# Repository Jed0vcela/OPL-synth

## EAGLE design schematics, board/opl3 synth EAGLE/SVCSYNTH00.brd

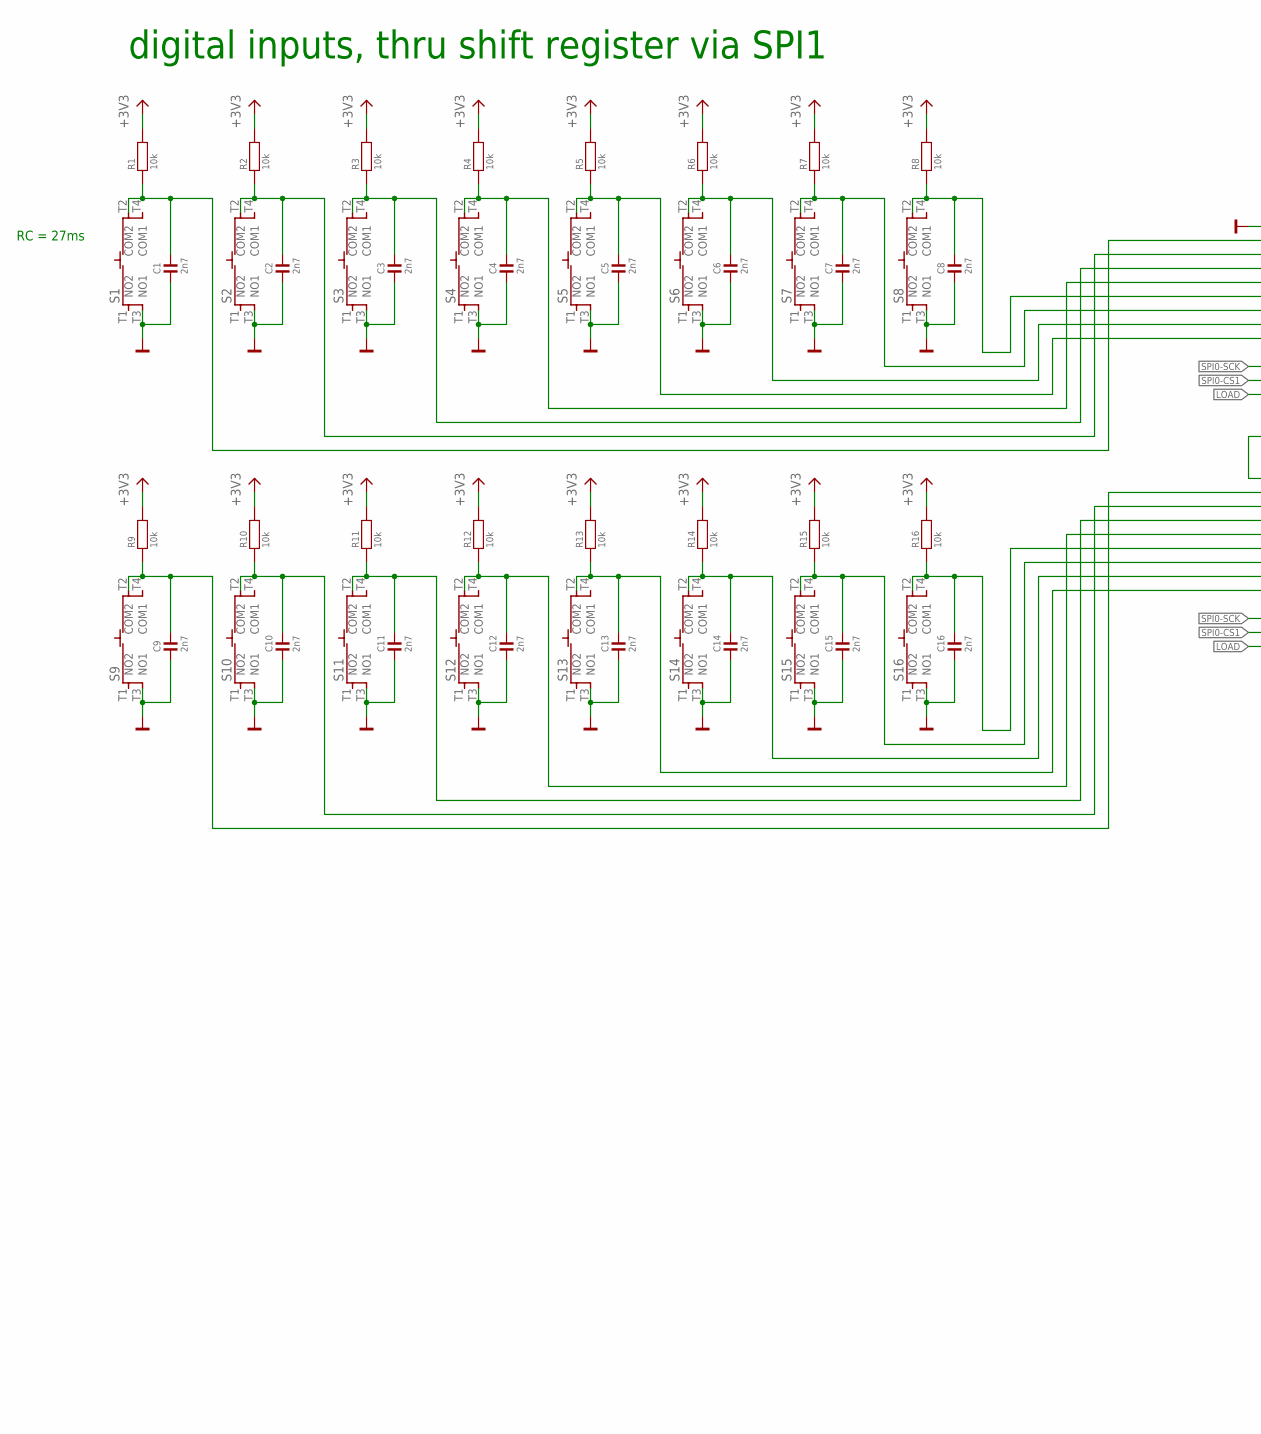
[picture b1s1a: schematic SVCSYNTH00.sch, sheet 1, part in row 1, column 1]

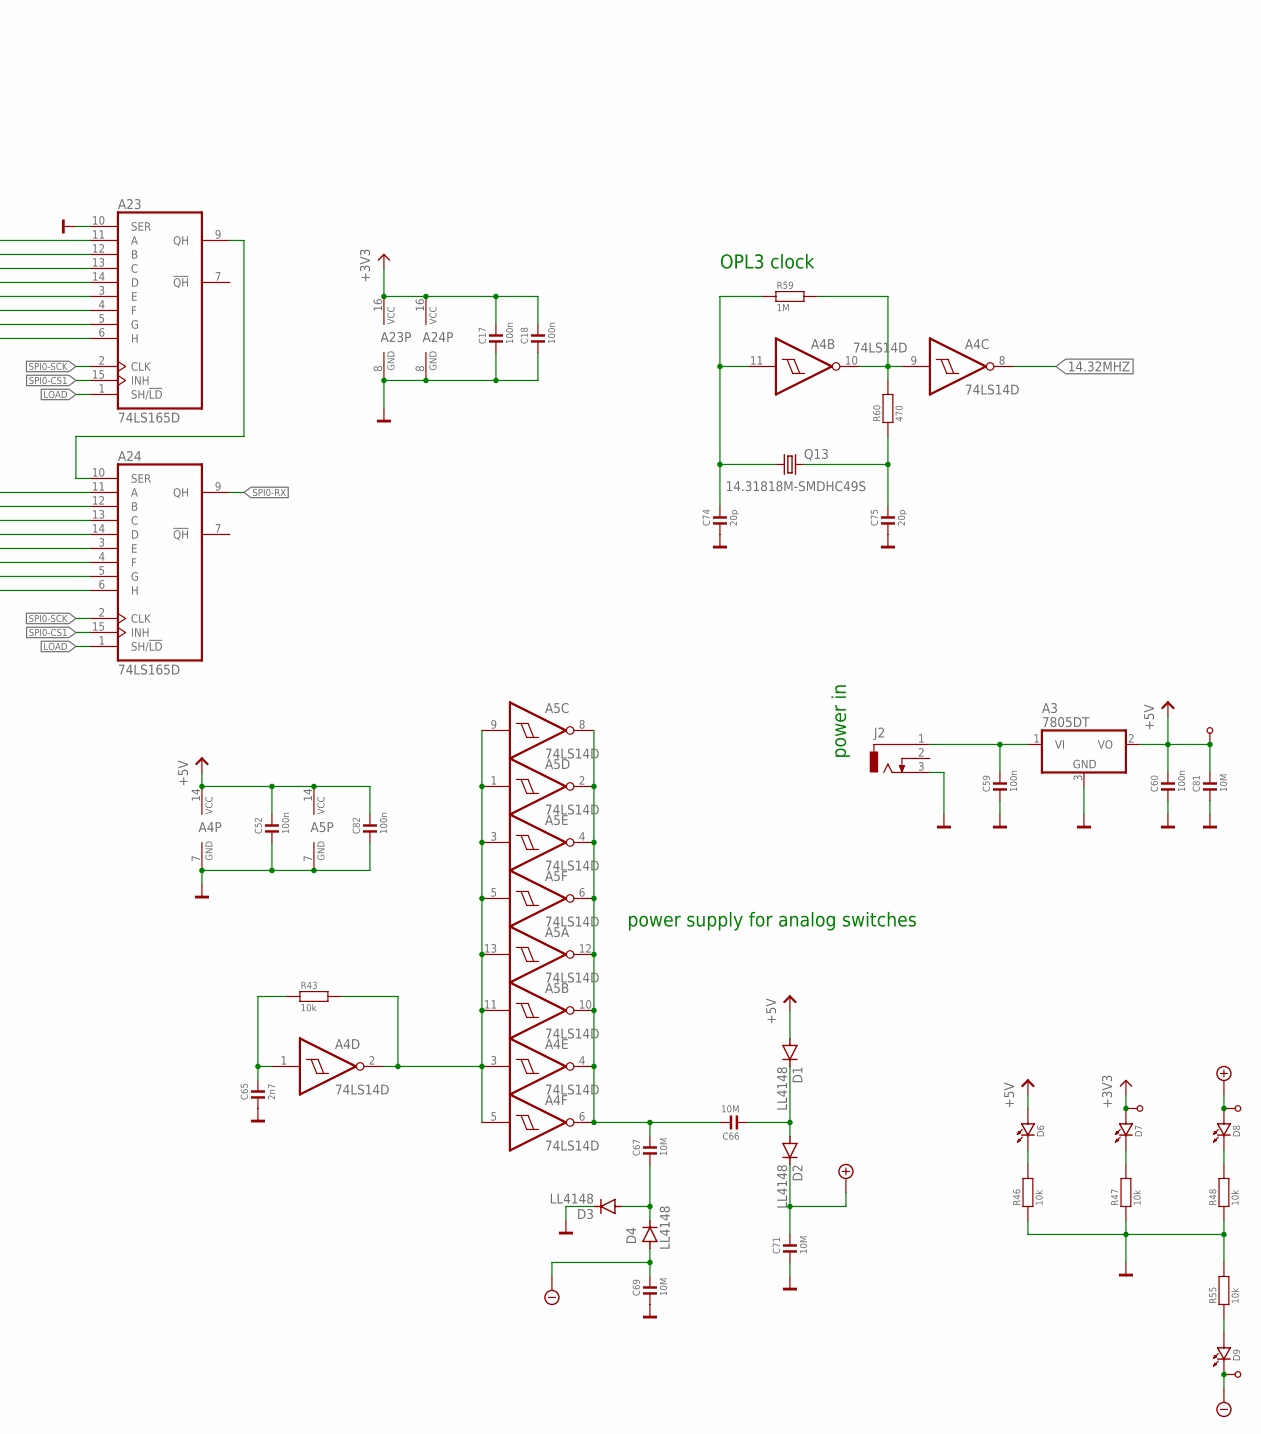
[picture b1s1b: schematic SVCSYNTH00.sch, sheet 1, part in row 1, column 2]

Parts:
A3: 7805DT; TO252
A4, A5: 74LS14D; SO14
A23, A24: 74LS165D; SO16
C1, C2, C3, C4, C5, C6, C7, C8, C9, C10, C11, C12, C13, C14, C15, C16, C65: 2n7; R0805
C17, C18, C52, C59, C60, C82: 100n; R0805
C66, C67, C69, C71, C81: 10M; R1206
C74, C75: 20p; R0805
D1, D2, D3, D4: LL4148; SOD80C
D6, D7, D8, D9: LED3MM
J2: DCJ0303
K1, K2, K3, K4: K1_0.9_1.8; K_0.9_1.8
Q13: 14.31818M-SMDHC49S; CSM-7X-DU
R1, R2, R3, R4, R5, R6, R7, R8, R9, R10, R11, R12, R13, R14, R15, R16, R43, R46, R47, R48, R55: 10k; R0805
R59: 1M; R0805
R60: 470; R0805
S1, S2, S3, S4, S5, S6, S7, S8, S9, S10, S11, S12, S13, S14, S15, S16: 101-TS6211T1603-EV; 101TS6211T1603EV

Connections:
14.32MHZ: A4.8 (O); also elsewhere on the board
+3V3: A23.16 (VCC), A24.16 (VCC), C17.2, C18.2, D7.A, K4.1, R1.1 (2), R2.1 (2), R3.1 (2), R4.1 (2), R5.1 (2), R6.1 (2), R7.1 (2), R8.1 (2), R9.1 (2), R10.1 (2), R11.1 (2), R12.1 (2), R13.1 (2), R14.1 (2), R15.1 (2), R16.1 (2); also elsewhere on the board
+5V: A3.2 (VO), A4.14 (VCC), A5.14 (VCC), C52.2, C60.2, C81.2, C82.2, D1.A, D6.A, K1.1; also elsewhere on the board
+9V: C71.2, D2.C, D8.A, K2.1; also elsewhere on the board
-5V: C69.2, D4.A, D9.K (C), K3.1; also elsewhere on the board
GND: A3.3 (GND), A4.7 (GND), A5.7 (GND), A23.8 (GND), A23.10 (SER), A24.8 (GND), C1.1, C2.1, C3.1, C4.1, C5.1, C6.1, C7.1, C8.1, C9.1, C10.1, C11.1, C12.1, C13.1, C14.1, C15.1, C16.1, C17.1, C18.1, C52.1, C59.1, C60.1, C65.1, C69.1, C71.1, C74.1, C75.1, C81.1, C82.1, D3.C, J2.3, R46.2 (1), R47.2 (1), R48.2 (1), R55.1 (2), S1.T3 (NO1), S2.T3 (NO1), S3.T3 (NO1), S4.T3 (NO1), S5.T3 (NO1), S6.T3 (NO1), S7.T3 (NO1), S8.T3 (NO1), S9.T3 (NO1), S10.T3 (NO1), S11.T3 (NO1), S12.T3 (NO1), S13.T3 (NO1), S14.T3 (NO1), S15.T3 (NO1), S16.T3 (NO1); also elsewhere on the board
LOAD: A23.1 (SH/!LD), A24.1 (SH/!LD); also elsewhere on the board
unnamed: A4.11 (I), C74.2, Q13.1, R59.2 (1)
unnamed: C75.2, Q13.2, R60.2 (1)
unnamed: A4.9 (I), A4.10 (O), R59.1 (2), R60.1 (2)
unnamed: A4.1 (I), C65.2, R43.2 (1)
unnamed: A4.2 (O), A4.3 (I), A4.5 (I), A5.1 (I), A5.3 (I), A5.5 (I), A5.9 (I), A5.11 (I), A5.13 (I), R43.1 (2)
unnamed: A4.4 (O), A4.6 (O), A5.2 (O), A5.4 (O), A5.6 (O), A5.8 (O), A5.10 (O), A5.12 (O), C66.2, C67.2
unnamed: C67.1, D3.A, D4.C
unnamed: C66.1, D1.C, D2.A
unnamed: A23.11 (A), C1.2, R1.2 (1), S1.T2 (COM2)
unnamed: A23.9 (QH), A24.10 (SER)
unnamed: A23.12 (B), C2.2, R2.2 (1), S2.T2 (COM2)
unnamed: A23.13 (C), C3.2, R3.2 (1), S3.T2 (COM2)
unnamed: A23.14 (D), C4.2, R4.2 (1), S4.T2 (COM2)
unnamed: A24.11 (A), C9.2, R9.2 (1), S9.T2 (COM2)
unnamed: A24.12 (B), C10.2, R10.2 (1), S10.T2 (COM2)
unnamed: A24.13 (C), C11.2, R11.2 (1), S11.T2 (COM2)
unnamed: A24.14 (D), C12.2, R12.2 (1), S12.T2 (COM2)
unnamed: A23.6 (H), C5.2, R5.2 (1), S5.T2 (COM2)
unnamed: A23.5 (G), C6.2, R6.2 (1), S6.T2 (COM2)
unnamed: A23.4 (F), C7.2, R7.2 (1), S7.T2 (COM2)
unnamed: A23.3 (E), C8.2, R8.2 (1), S8.T2 (COM2)
unnamed: A24.6 (H), C13.2, R13.2 (1), S13.T2 (COM2)
unnamed: A24.5 (G), C14.2, R14.2 (1), S14.T2 (COM2)
unnamed: A24.4 (F), C15.2, R15.2 (1), S15.T2 (COM2)
unnamed: A24.3 (E), C16.2, R16.2 (1), S16.T2 (COM2)
unnamed: A3.1 (VI), C59.2, J2.1
unnamed: D6.K (C), R46.1 (2)
unnamed: D7.K (C), R47.1 (2)
unnamed: D8.K (C), R48.1 (2)
unnamed: D9.A, R55.2 (1)
SPI0-CS1: A23.15 (INH), A24.15 (INH); also elsewhere on the board
SPI0-RX: A24.9 (QH); also elsewhere on the board
SPI0-SCK: A23.2 (CLK), A24.2 (CLK); also elsewhere on the board

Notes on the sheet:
RC = 27ms
digital inputs, thru shift register via SPI1
OPL3 clock
power supply for analog switches
power in

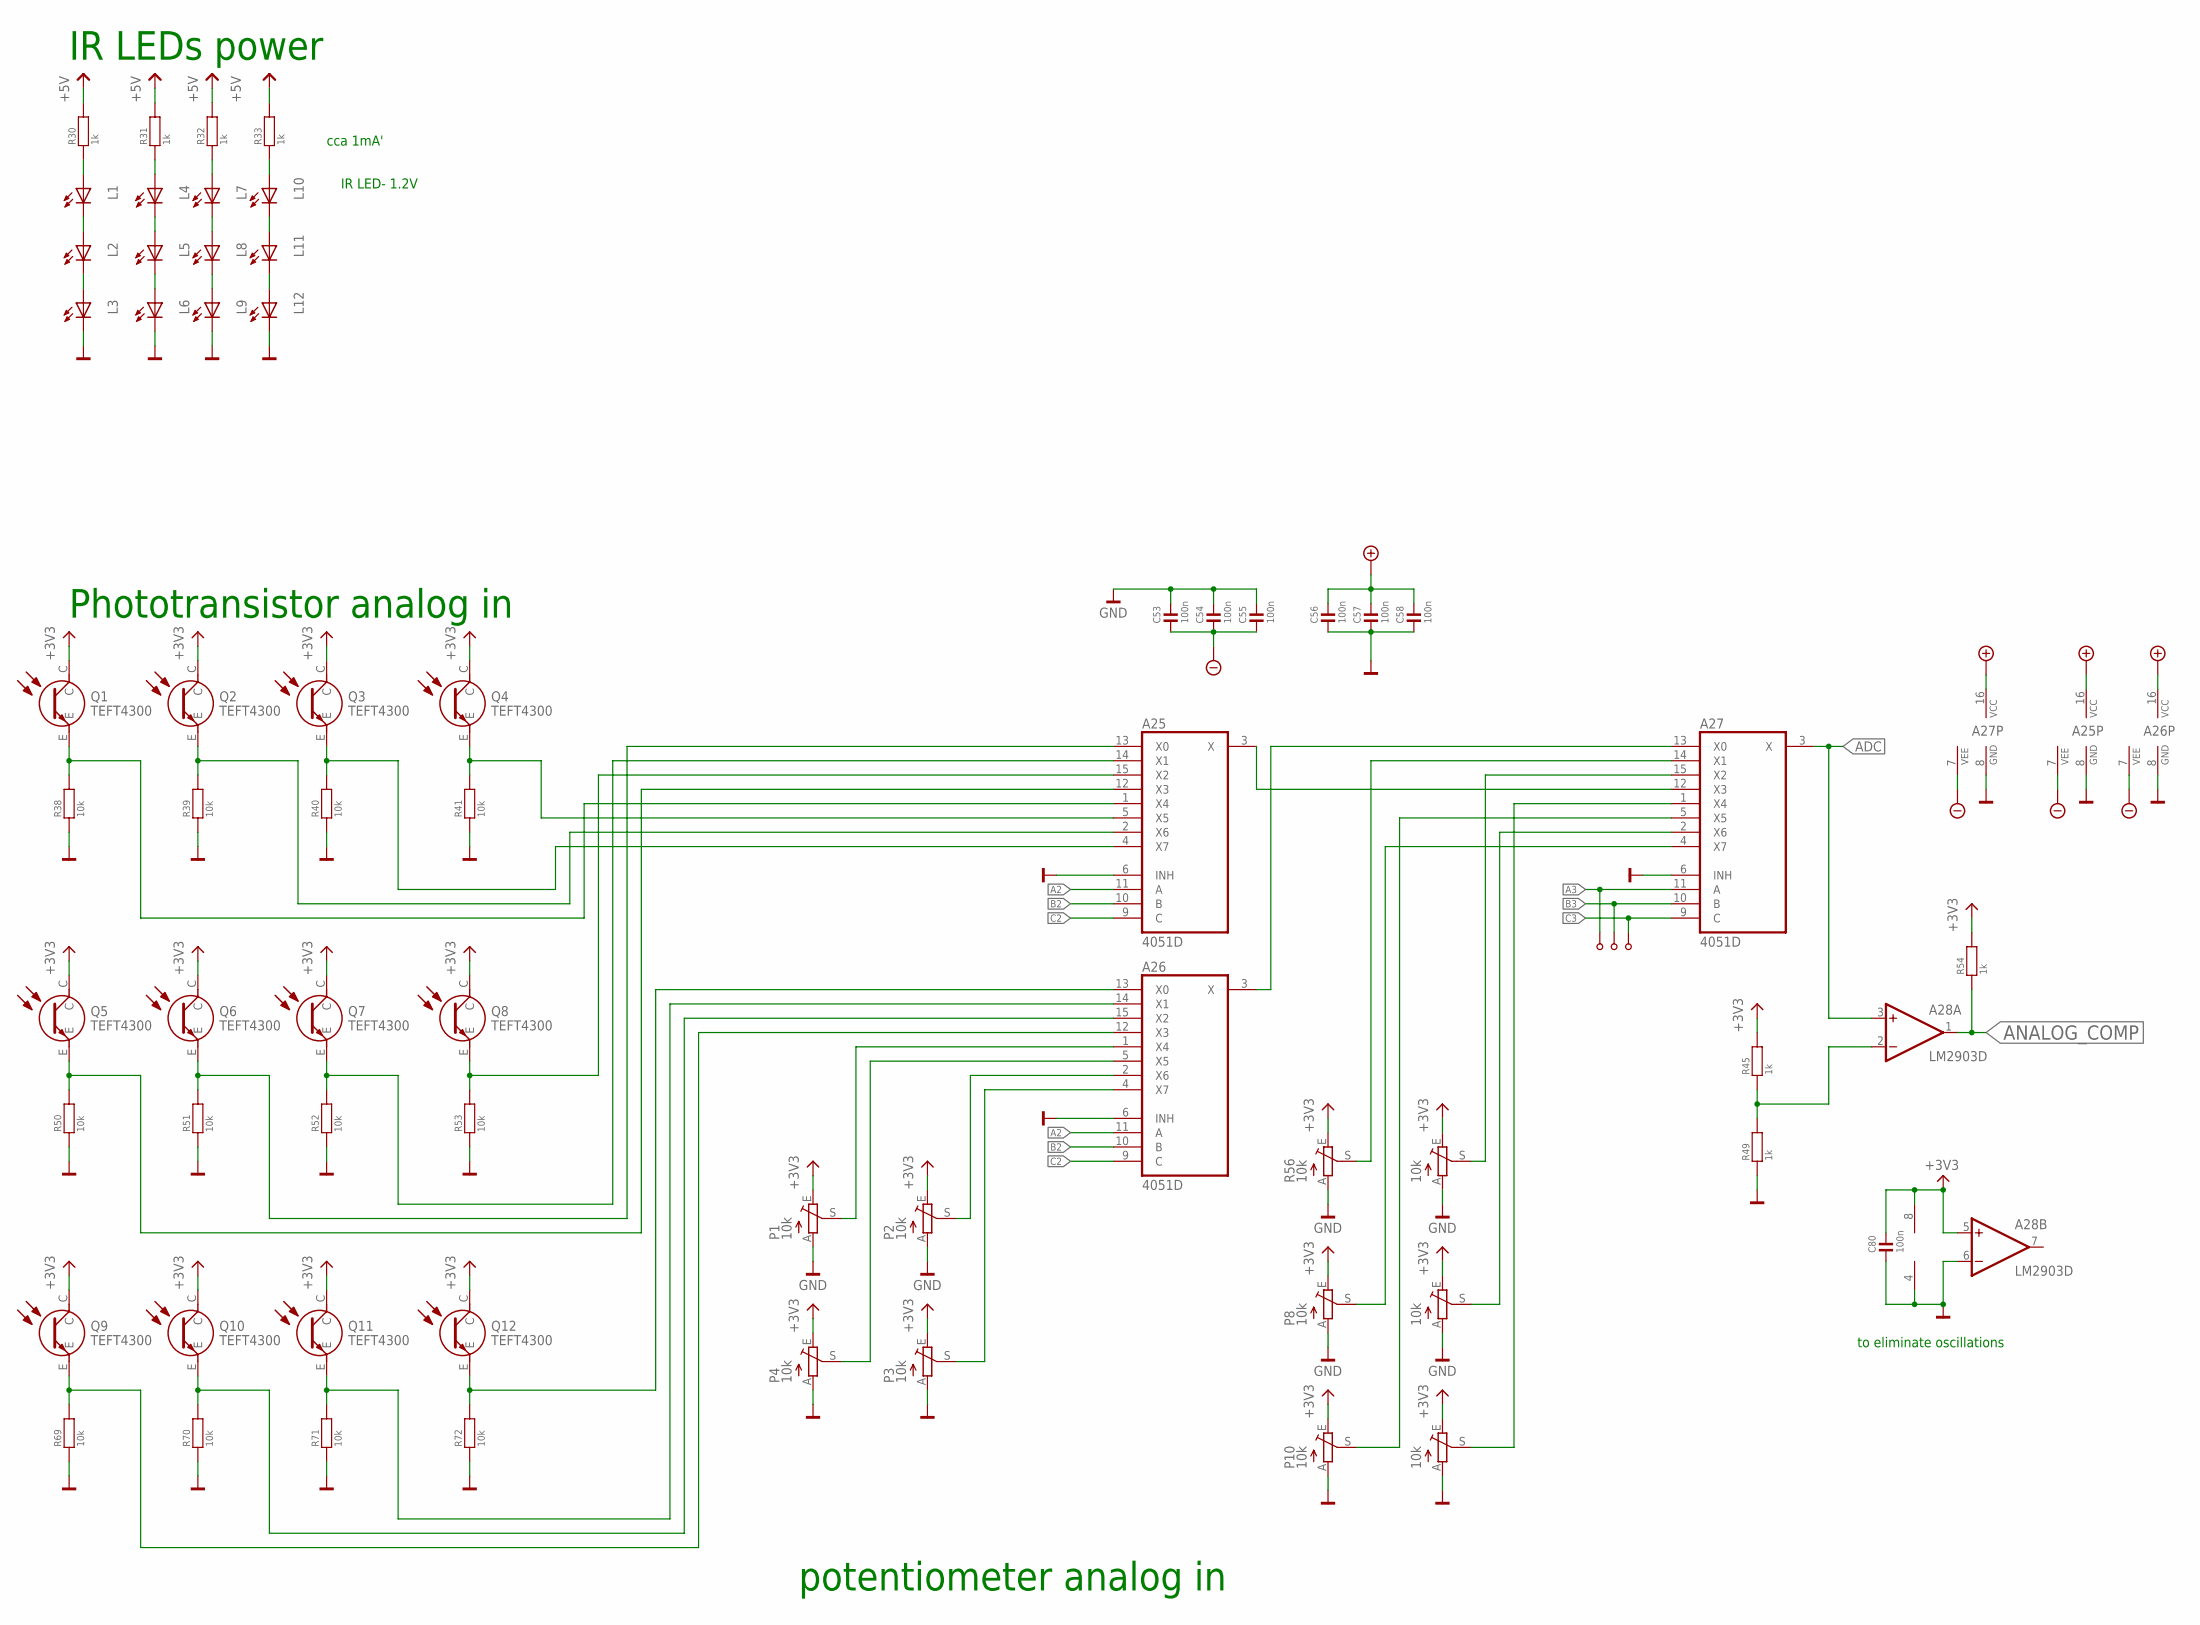
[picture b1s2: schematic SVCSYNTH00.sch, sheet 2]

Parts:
A25, A26, A27: 4051D; SO16
A28: LM2903D; SO08
C53, C54, C55, C56, C57, C58, C80: 100n; R0805
K8, K9, K10: K1_0.8_1.6; K_0.8_1.6
L1, L2, L3, L4, L5, L6, L7, L8, L9, L10, L11, L12: LED3MM
P1, P2, P3, P4, P6, P8, P10: 10k; CA6V
Q1, Q2, Q3, Q4, Q5, Q6, Q7, Q8, Q9, Q10, Q11, Q12: TEFT4300
R30, R31, R32, R33, R45, R49, R54: 1k; R0805
R38, R39, R40, R41, R50, R51, R52, R53, R69, R70, R71, R72: 10k; R0805
R56, R57, R74: 10k; CA6V

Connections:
+3V3: A28.5 (+IN), A28.8 (V+), C80.2, P1.E, P2.E, P3.E, P4.E, P6.E, P8.E, P10.E, Q1.C, Q2.C, Q3.C, Q4.C, Q5.C, Q6.C, Q7.C, Q8.C, Q9.C, Q10.C, Q11.C, Q12.C, R45.1 (2), R54.1 (2), R56.E, R57.E, R74.E; also elsewhere on the board
+5V: R30.1 (2), R31.1 (2), R32.1 (2), R33.1 (2); also elsewhere on the board
+9V: A25.16 (VCC), A26.16 (VCC), A27.16 (VCC), C56.2, C57.2, C58.2; also elsewhere on the board
-5V: A25.7 (VEE), A26.7 (VEE), A27.7 (VEE), C53.1, C54.1, C55.1; also elsewhere on the board
A2: A25.11 (A), A26.11 (A); also elsewhere on the board
A3: A27.11 (A), K8.1; also elsewhere on the board
ADC: A27.3 (X), A28.3 (+IN); also elsewhere on the board
ANALOG_COMP: A28.1 (OUT), R54.2 (1); also elsewhere on the board
B2: A25.10 (B), A26.10 (B); also elsewhere on the board
B3: A27.10 (B), K9.1; also elsewhere on the board
C2: A25.9 (C), A26.9 (C); also elsewhere on the board
C3: A27.9 (C), K10.1; also elsewhere on the board
GND: A25.6 (INH), A25.8 (GND), A26.6 (INH), A26.8 (GND), A27.6 (INH), A27.8 (GND), A28.4 (V-), A28.6 (-IN), C53.2, C54.2, C55.2, C56.1, C57.1, C58.1, C80.1, L3.K (C), L6.K (C), L9.K (C), L12.K (C), P1.A, P2.A, P3.A, P4.A, P6.A, P8.A, P10.A, R38.2 (1), R39.2 (1), R40.2 (1), R41.2 (1), R49.2 (1), R50.2 (1), R51.2 (1), R52.2 (1), R53.2 (1), R56.A, R57.A, R69.2 (1), R70.2 (1), R71.2 (1), R72.2 (1), R74.A; also elsewhere on the board
unnamed: A25.3 (X), A27.12 (X3)
unnamed: A26.3 (X), A27.13 (X0)
unnamed: A27.14 (X1), R56.S
unnamed: A27.4 (X7), P8.S
unnamed: A27.5 (X5), P10.S
unnamed: A27.15 (X2), R57.S
unnamed: L1.A, R30.2 (1)
unnamed: L1.K (C), L2.A
unnamed: L2.K (C), L3.A
unnamed: A25.5 (X5), Q4.E, R41.1 (2)
unnamed: L5.K (C), L6.A
unnamed: L4.K (C), L5.A
unnamed: L4.A, R31.2 (1)
unnamed: L7.A, R32.2 (1)
unnamed: L7.K (C), L8.A
unnamed: L8.K (C), L9.A
unnamed: L11.K (C), L12.A
unnamed: L10.K (C), L11.A
unnamed: A25.4 (X7), Q3.E, R40.1 (2)
unnamed: A25.2 (X6), Q2.E, R39.1 (2)
unnamed: A25.1 (X4), Q1.E, R38.1 (2)
unnamed: A25.15 (X2), Q8.E, R53.1 (2)
unnamed: A25.14 (X1), Q7.E, R52.1 (2)
unnamed: A25.13 (X0), Q6.E, R51.1 (2)
unnamed: A25.12 (X3), Q5.E, R50.1 (2)
unnamed: A26.13 (X0), Q12.E, R72.1 (2)
unnamed: A26.14 (X1), Q11.E, R71.1 (2)
unnamed: A26.15 (X2), Q10.E, R70.1 (2)
unnamed: A26.12 (X3), Q9.E, R69.1 (2)
unnamed: A26.1 (X4), P1.S
unnamed: A26.5 (X5), P4.S
unnamed: A26.2 (X6), P2.S
unnamed: A26.4 (X7), P3.S
unnamed: A27.2 (X6), P6.S
unnamed: A27.1 (X4), R74.S
unnamed: A28.2 (-IN), R45.2 (1), R49.1 (2)
unnamed: L10.A, R33.2 (1)

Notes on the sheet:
Phototransistor analog in
potentiometer analog in
to eliminate oscillations
IR LED- 1.2V
cca 1mA'
IR LEDs power

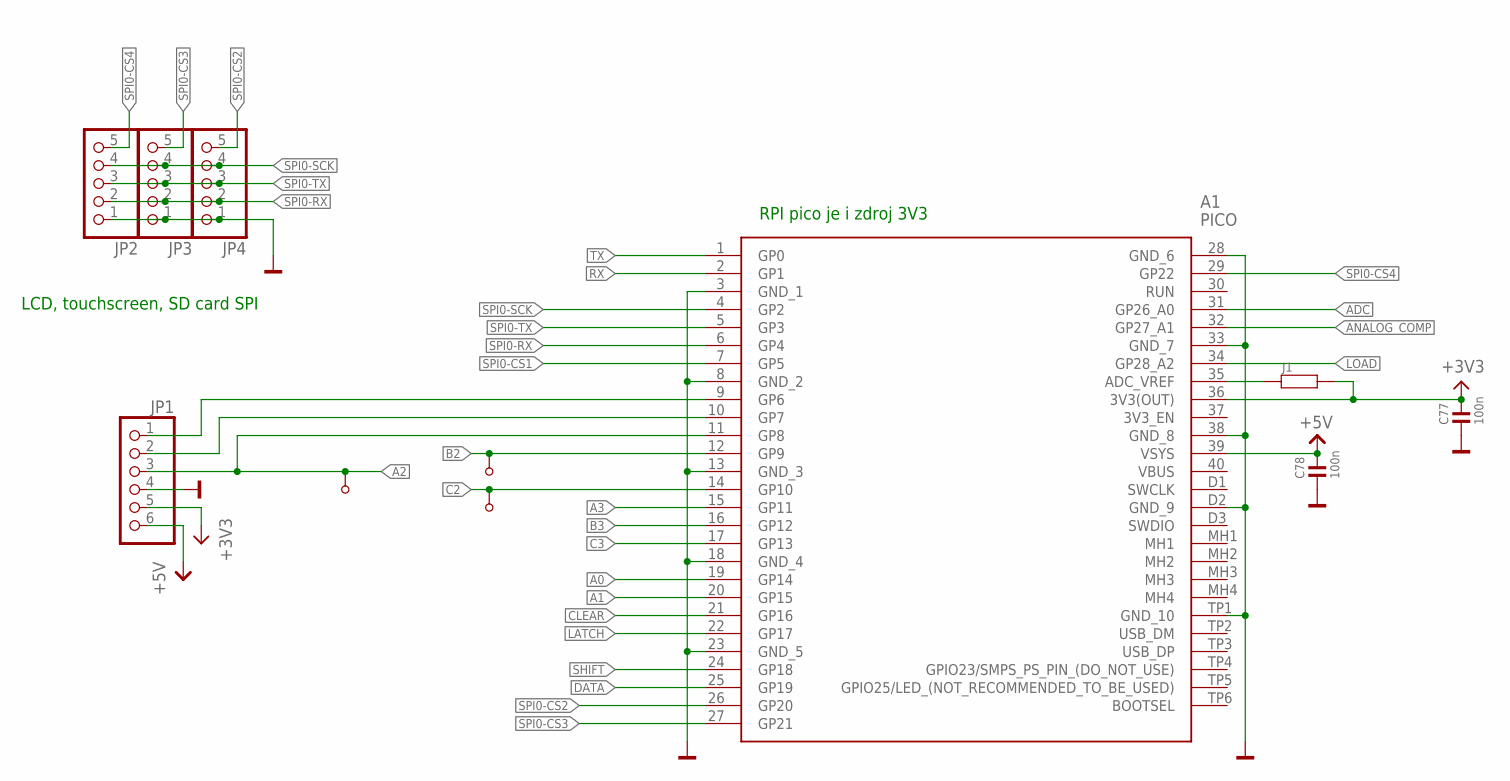
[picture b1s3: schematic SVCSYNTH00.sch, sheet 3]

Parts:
A1: PICO
C77, C78: 100n; R0805
J1: R0402
JP1: PINHD-1X6; 1X06
JP2, JP3, JP4: PINHD-1X5; 1X05
K5, K6, K7: K1_1.0_2.2; K_1.0_2.2

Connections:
+3V3: A1.36 (3V3(OUT)), C77.2, J1.2, JP1.5; also elsewhere on the board
+5V: A1.39 (VSYS), C78.2, JP1.6; also elsewhere on the board
A0: A1.19 (GP14); also elsewhere on the board
A1: A1.20 (GP15); also elsewhere on the board
A2: A1.11 (GP8), JP1.3, K5.1; also elsewhere on the board
A3: A1.15 (GP11); also elsewhere on the board
ADC: A1.31 (GP26_A0); also elsewhere on the board
ANALOG_COMP: A1.32 (GP27_A1); also elsewhere on the board
B2: A1.12 (GP9), K7.1; also elsewhere on the board
B3: A1.16 (GP12); also elsewhere on the board
C2: A1.14 (GP10), K6.1; also elsewhere on the board
C3: A1.17 (GP13); also elsewhere on the board
CLEAR: A1.21 (GP16); also elsewhere on the board
DATA: A1.25 (GP19); also elsewhere on the board
GND: A1.3 (GND_1), A1.8 (GND_2), A1.13 (GND_3), A1.18 (GND_4), A1.23 (GND_5), A1.28 (GND_6), A1.33 (GND_7), A1.38 (GND_8), A1.D2 (GND_9), A1.TP1 (GND_10), C77.1, C78.1, JP1.4, JP2.1, JP3.1, JP4.1; also elsewhere on the board
LATCH: A1.22 (GP17); also elsewhere on the board
LOAD: A1.34 (GP28_A2); also elsewhere on the board
unnamed: A1.35 (ADC_VREF), J1.1
unnamed: A1.9 (GP6), JP1.1
unnamed: A1.10 (GP7), JP1.2
RX: A1.2 (GP1); also elsewhere on the board
SHIFT: A1.24 (GP18); also elsewhere on the board
SPI0-CS1: A1.7 (GP5); also elsewhere on the board
SPI0-CS2: A1.26 (GP20), JP4.5
SPI0-CS3: A1.27 (GP21), JP3.5
SPI0-CS4: A1.29 (GP22), JP2.5
SPI0-RX: A1.6 (GP4), JP2.2, JP3.2, JP4.2; also elsewhere on the board
SPI0-SCK: A1.4 (GP2), JP2.4, JP3.4, JP4.4; also elsewhere on the board
SPI0-TX: A1.5 (GP3), JP2.3, JP3.3, JP4.3
TX: A1.1 (GP0); also elsewhere on the board

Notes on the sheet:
LCD, touchscreen, SD card SPI
RPI pico je i zdroj 3V3

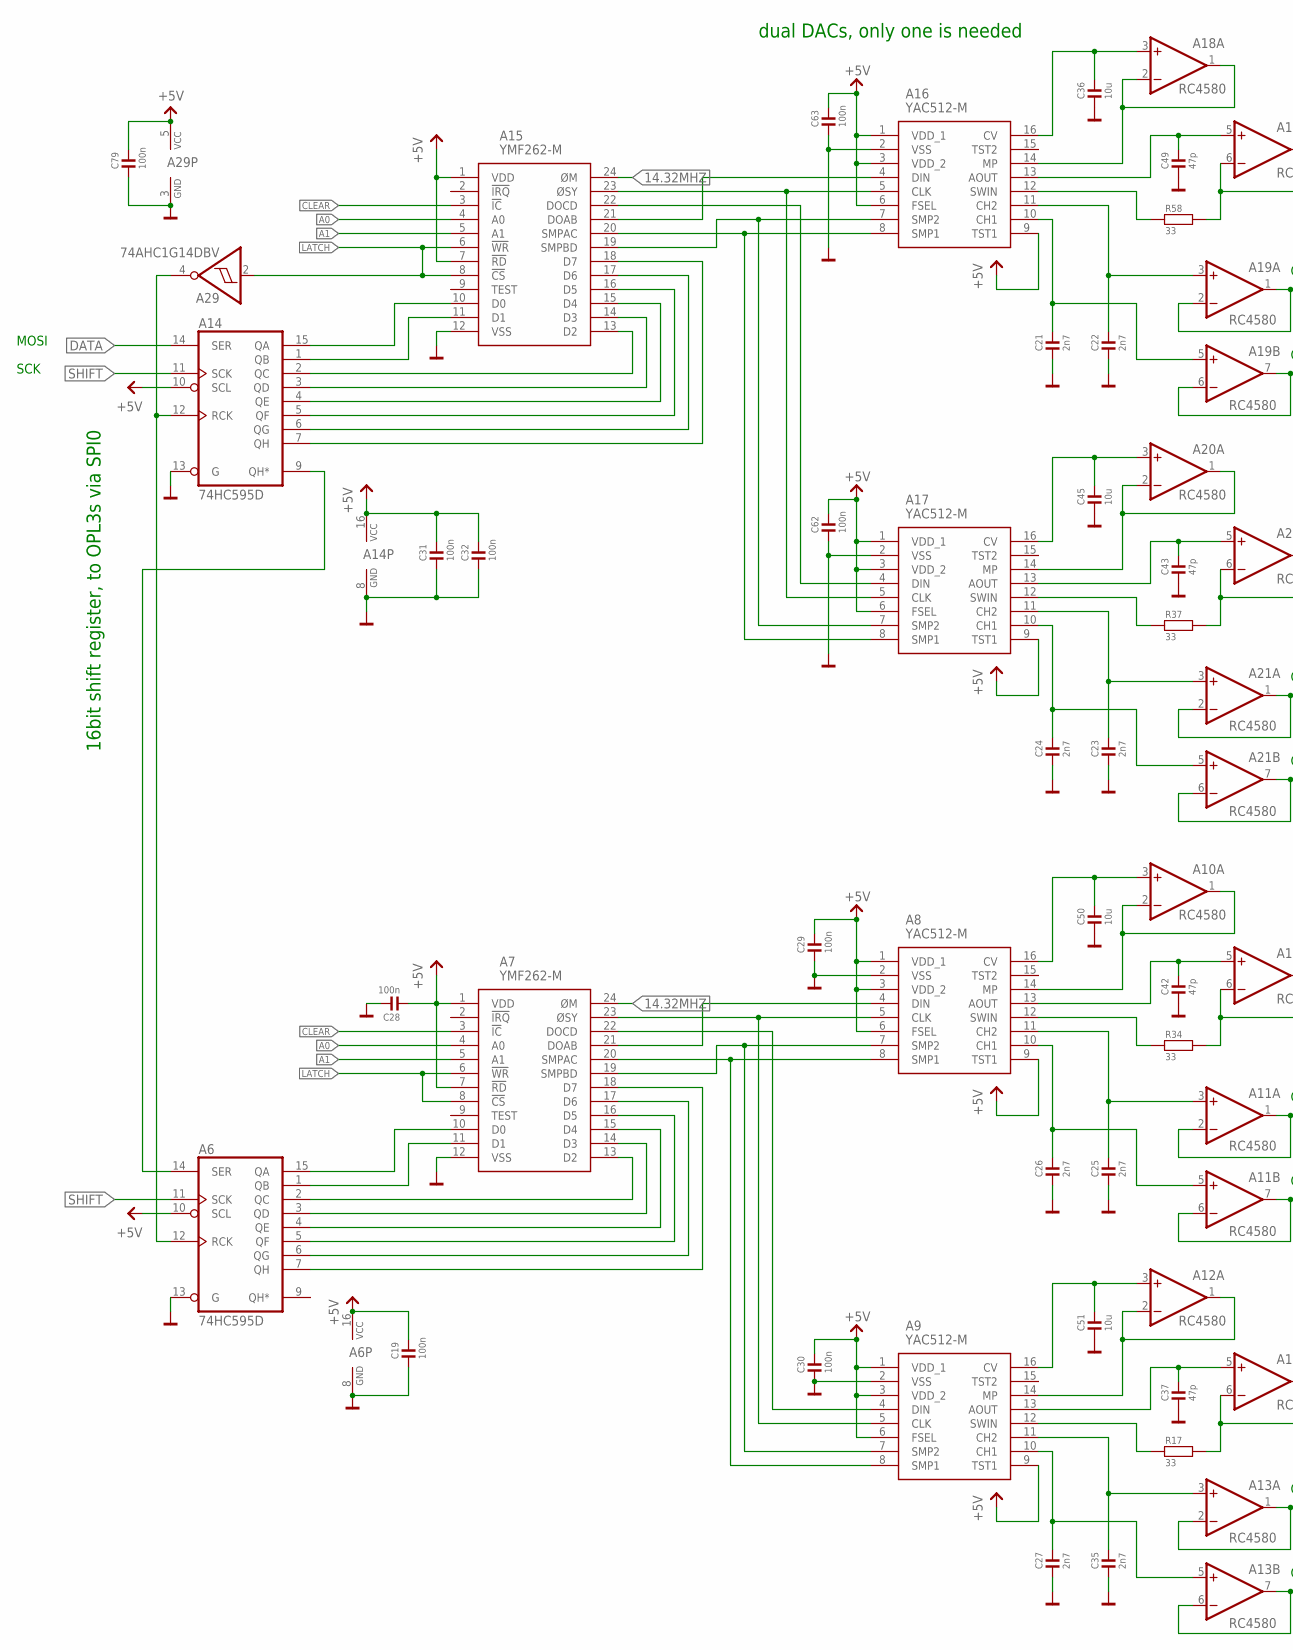
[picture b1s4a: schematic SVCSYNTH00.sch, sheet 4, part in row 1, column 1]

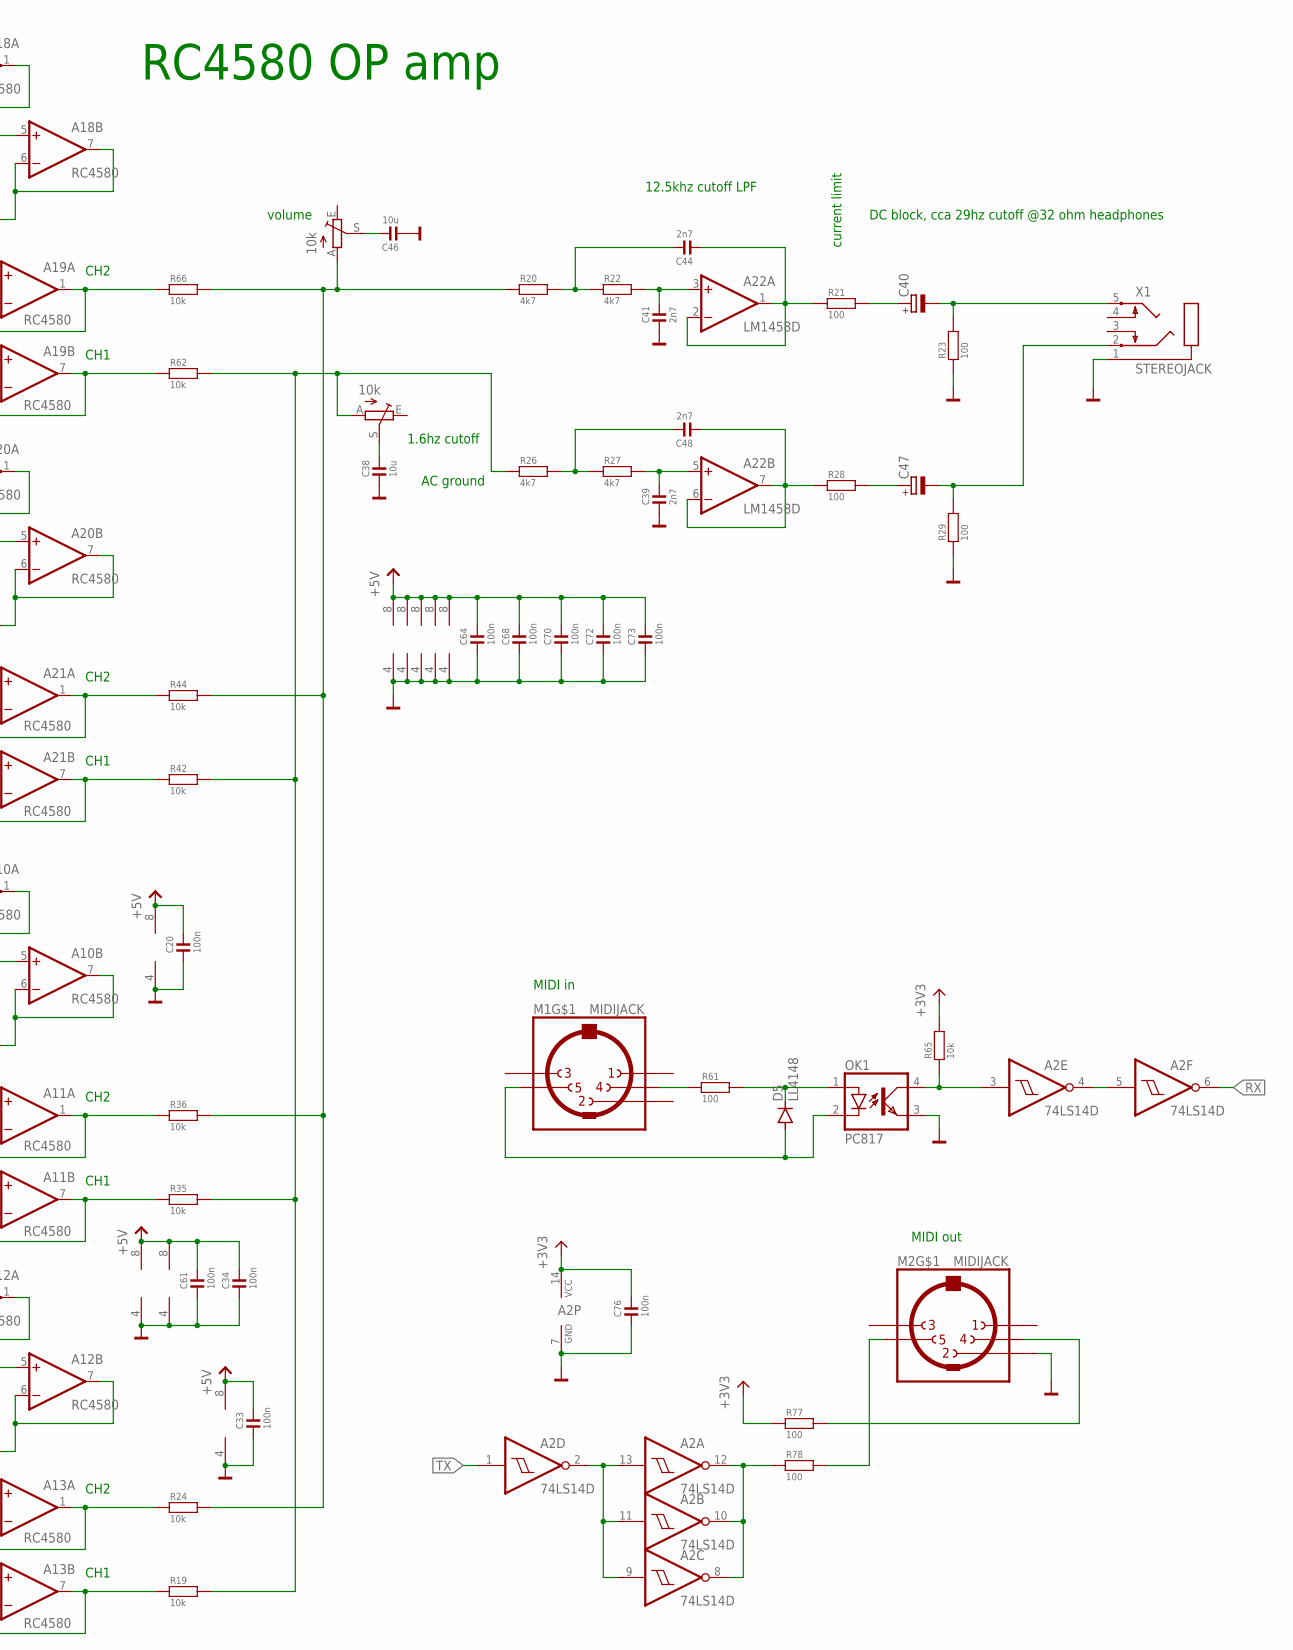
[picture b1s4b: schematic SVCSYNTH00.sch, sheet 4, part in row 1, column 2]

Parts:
A2: 74LS14D; SO14
A6, A14: 74HC595D; SO16
A7, A15: YMF262-M; SOIC127P1180X250-24N
A8, A9, A16, A17: YAC512-M; SOIC127P780X230-16N
A10, A11, A12, A13, A18, A19, A20, A21: RC4580; SO08
A22: LM1458D; SO08
A29: 74AHC1G14DBV; SOT23-5
C19, C20, C28, C29, C30, C31, C32, C33, C34, C61, C62, C63, C64, C68, C70, C72, C73, C76, C79: 100n; R0805
C21, C22, C23, C24, C25, C26, C27, C35, C39, C41, C44, C48: 2n7; R0805
C36, C38, C45, C46, C50, C51: 10u; R0805
C37, C42, C43, C49: 47p; R0805
C40, C47: CPOL-EUE3.5-8; E3,5-8
D5: LL4148; SOD80C
M1, M2: MIDIJACK; CP-2350
OK1: PC817; DIL04
R17, R34, R37, R58: 33; R0805
R18, R25: 10k; CA6V
R19, R24, R35, R36, R42, R44, R62, R65, R66: 10k; R0805
R20, R22, R26, R27: 4k7; R0805
R21, R23, R28, R29, R61, R77, R78: 100; R0805
X1: STEREOJACK; STX3100

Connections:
14.32MHZ: A7.24 (ØM), A15.24 (ØM); also elsewhere on the board
+3V3: A2.14 (VCC), C76.2, R65.1 (2), R77.2 (1); also elsewhere on the board
+5V: A6.10 (SCL), A6.16 (VCC), A7.1 (VDD), A7.7 (!RD), A8.1 (VDD_1), A8.3 (VDD_2), A8.6 (FSEL), A8.9 (TST1), A9.1 (VDD_1), A9.3 (VDD_2), A9.6 (FSEL), A9.9 (TST1), A10.8 (V+), A11.8 (V+), A12.8 (V+), A13.8 (V+), A14.10 (SCL), A14.16 (VCC), A15.1 (VDD), A15.7 (!RD), A16.1 (VDD_1), A16.3 (VDD_2), A16.6 (FSEL), A16.9 (TST1), A17.1 (VDD_1), A17.3 (VDD_2), A17.6 (FSEL), A17.9 (TST1), A18.8 (V+), A19.8 (V+), A20.8 (V+), A21.8 (V+), A22.8 (V+), A29.5 (VCC), C19.2, C20.2, C28.1, C29.2, C30.2, C31.2, C32.2, C33.2, C34.2, C61.2, C62.2, C63.2, C64.2, C68.2, C70.2, C72.2, C73.2, C79.2; also elsewhere on the board
A0: A7.4 (A0), A15.4 (A0); also elsewhere on the board
A1: A7.5 (A1), A15.5 (A1); also elsewhere on the board
CLEAR: A7.3 (!IC), A15.3 (!IC); also elsewhere on the board
DATA: A14.14 (SER); also elsewhere on the board
GND: A2.7 (GND), A6.8 (GND), A6.13 (G), A7.12 (VSS), A8.2 (VSS), A9.2 (VSS), A10.4 (V-), A11.4 (V-), A12.4 (V-), A13.4 (V-), A14.8 (GND), A14.13 (G), A15.12 (VSS), A16.2 (VSS), A17.2 (VSS), A18.4 (V-), A19.4 (V-), A20.4 (V-), A21.4 (V-), A22.4 (V-), A29.3 (GND), C19.1, C20.1, C21.1, C22.1, C23.1, C24.1, C25.1, C26.1, C27.1, C28.2, C29.1, C30.1, C31.1, C32.1, C33.1, C34.1, C35.1, C36.1, C37.1, C38.1, C39.1, C41.1, C42.1, C43.1, C45.1, C46.1, C49.1, C50.1, C51.1, C61.1, C62.1, C63.1, C64.1, C68.1, C70.1, C72.1, C73.1, C76.1, C79.1, M2.2, OK1.3 (EMIT), R23.2 (1), R29.2 (1), X1.1; also elsewhere on the board
LATCH: A7.6 (!WR), A7.8 (!CS), A15.6 (!WR), A15.8 (!CS), A29.2 (I); also elsewhere on the board
unnamed: A16.13 (AOUT), A18.5 (+IN), C49.2
unnamed: A16.14 (MP), A18.1 (OUT), A18.2 (-IN)
unnamed: A16.16 (CV), A18.3 (+IN), C36.2
unnamed: A18.6 (-IN), A18.7 (OUT), R58.1 (2)
unnamed: A16.12 (SWIN), R58.2 (1)
unnamed: A16.10 (CH1), A19.5 (+IN), C21.2
unnamed: A16.11 (CH2), A19.3 (+IN), C22.2
unnamed: A19.1 (OUT), A19.2 (-IN), R66.2 (1)
unnamed: A19.6 (-IN), A19.7 (OUT), R62.2 (1)
unnamed: A14.15 (QA), A15.10 (D0)
unnamed: A14.1 (QB), A15.11 (D1)
unnamed: A14.2 (QC), A15.13 (D2)
unnamed: A14.3 (QD), A15.14 (D3)
unnamed: A14.4 (QE), A15.15 (D4)
unnamed: A14.5 (QF), A15.16 (D5)
unnamed: A14.6 (QG), A15.17 (D6)
unnamed: A14.7 (QH), A15.18 (D7)
unnamed: A15.20 (SMPAC), A16.8 (SMP1), A17.8 (SMP1)
unnamed: A8.14 (MP), A10.1 (OUT), A10.2 (-IN)
unnamed: A15.21 (DOAB), A16.4 (DIN)
unnamed: A15.23 (ØSY), A16.5 (CLK), A17.5 (CLK)
unnamed: A17.14 (MP), A20.1 (OUT), A20.2 (-IN)
unnamed: A6.12 (RCK), A14.12 (RCK), A29.4 (O)
unnamed: A17.16 (CV), A20.3 (+IN), C45.2
unnamed: A17.13 (AOUT), A20.5 (+IN), C43.2
unnamed: A20.6 (-IN), A20.7 (OUT), R37.1 (2)
unnamed: A17.12 (SWIN), R37.2 (1)
unnamed: A17.10 (CH1), A21.5 (+IN), C24.2
unnamed: A17.11 (CH2), A21.3 (+IN), C23.2
unnamed: A21.1 (OUT), A21.2 (-IN), R44.2 (1)
unnamed: A21.6 (-IN), A21.7 (OUT), R42.2 (1)
unnamed: A15.19 (SMPBD), A16.7 (SMP2), A17.7 (SMP2)
unnamed: A15.22 (DOCD), A17.4 (DIN)
unnamed: A8.16 (CV), A10.3 (+IN), C50.2
unnamed: A8.13 (AOUT), A10.5 (+IN), C42.2
unnamed: A10.6 (-IN), A10.7 (OUT), R34.1 (2)
unnamed: A8.12 (SWIN), R34.2 (1)
unnamed: A8.10 (CH1), A11.5 (+IN), C26.2
unnamed: A8.11 (CH2), A11.3 (+IN), C25.2
unnamed: A11.1 (OUT), A11.2 (-IN), R36.2 (1)
unnamed: A11.6 (-IN), A11.7 (OUT), R35.2 (1)
unnamed: A6.15 (QA), A7.10 (D0)
unnamed: A6.1 (QB), A7.11 (D1)
unnamed: A6.2 (QC), A7.13 (D2)
unnamed: A6.3 (QD), A7.14 (D3)
unnamed: A6.4 (QE), A7.15 (D4)
unnamed: A6.5 (QF), A7.16 (D5)
unnamed: A6.6 (QG), A7.17 (D6)
unnamed: A6.7 (QH), A7.18 (D7)
unnamed: A7.20 (SMPAC), A8.8 (SMP1), A9.8 (SMP1)
unnamed: A7.21 (DOAB), A8.4 (DIN)
unnamed: A7.23 (ØSY), A8.5 (CLK), A9.5 (CLK)
unnamed: A9.14 (MP), A12.1 (OUT), A12.2 (-IN)
unnamed: A9.16 (CV), A12.3 (+IN), C51.2
unnamed: A9.13 (AOUT), A12.5 (+IN), C37.2
unnamed: A12.6 (-IN), A12.7 (OUT), R17.1 (2)
unnamed: A9.12 (SWIN), R17.2 (1)
unnamed: A9.10 (CH1), A13.5 (+IN), C27.2
unnamed: A9.11 (CH2), A13.3 (+IN), C35.2
unnamed: A13.1 (OUT), A13.2 (-IN), R24.2 (1)
unnamed: A13.6 (-IN), A13.7 (OUT), R19.2 (1)
unnamed: A7.19 (SMPBD), A8.7 (SMP2), A9.7 (SMP2)
unnamed: A7.22 (DOCD), A9.4 (DIN)
unnamed: A6.14 (SER), A14.9 (QH*)
unnamed: A22.3 (+IN), C41.2, R22.1 (2)
unnamed: R19.1 (2), R25.A, R26.2 (1), R35.1 (2), R42.1 (2), R62.1 (2)
unnamed: C38.2, R25.S
unnamed: R18.A, R20.2 (1), R24.1 (2), R36.1 (2), R44.1 (2), R66.1 (2)
unnamed: C46.2, R18.S
unnamed: C44.2, R20.1 (2), R22.2 (1)
unnamed: A22.5 (+IN), C39.2, R27.1 (2)
unnamed: A22.1 (OUT), A22.2 (-IN), C44.1, R21.2 (1)
unnamed: C48.2, R26.1 (2), R27.2 (1)
unnamed: A22.6 (-IN), A22.7 (OUT), C48.1, R28.2 (1)
unnamed: C40.+, R21.1 (2)
unnamed: C40.-, R23.1 (2), X1.5
unnamed: C47.+, R28.1 (2)
unnamed: C47.-, R29.1 (2), X1.2
unnamed: A2.2 (O), A2.9 (I), A2.11 (I), A2.13 (I)
unnamed: A2.4 (O), A2.5 (I)
unnamed: M2.5, R78.1 (2)
unnamed: A2.8 (O), A2.10 (O), A2.12 (O), R78.2 (1)
unnamed: M1.4, R61.2 (1)
unnamed: M2.4, R77.1 (2)
unnamed: D5.A, M1.5, OK1.2 (C)
unnamed: D5.C, OK1.1 (A), R61.1 (2)
unnamed: A2.3 (I), OK1.4 (COL), R65.2 (1)
RX: A2.6 (O); also elsewhere on the board
SHIFT: A6.11 (SCK), A14.11 (SCK); also elsewhere on the board
TX: A2.1 (I); also elsewhere on the board

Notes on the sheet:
CH1
CH2
MOSI
SCK
16bit shift register, to OPL3s via SPI0
dual DACs, only one is needed
1.6hz cutoff
AC ground
12.5khz cutoff LPF
RC4580 OP amp
volume
current limit
DC block, cca 29hz cutoff @32 ohm headphones
MIDI out
MIDI in
